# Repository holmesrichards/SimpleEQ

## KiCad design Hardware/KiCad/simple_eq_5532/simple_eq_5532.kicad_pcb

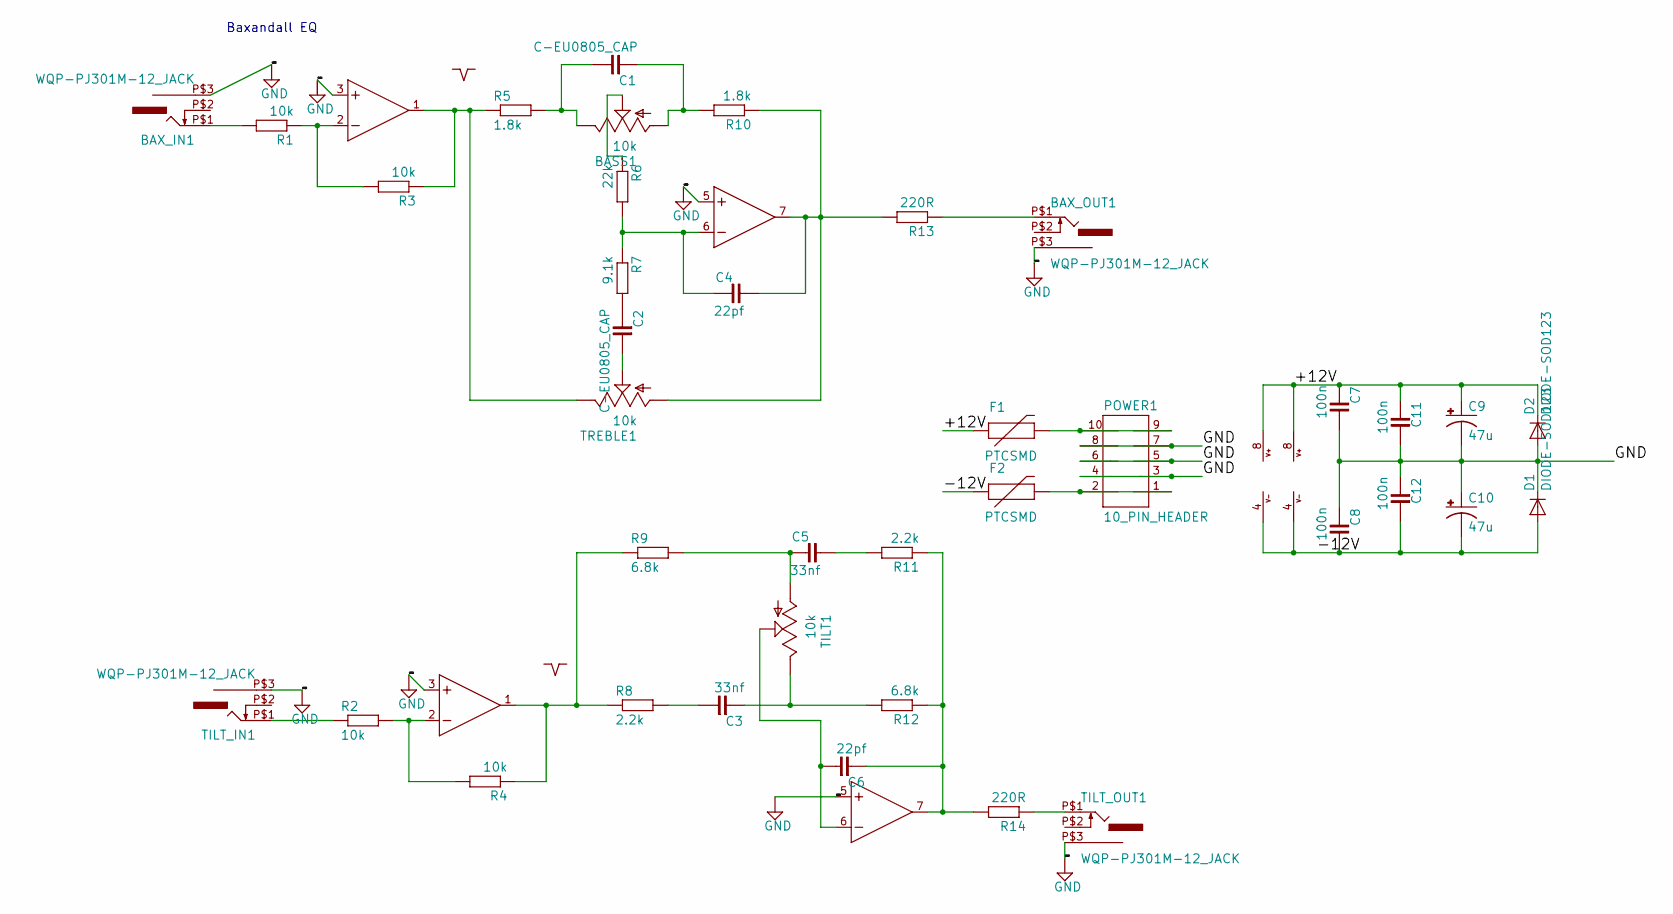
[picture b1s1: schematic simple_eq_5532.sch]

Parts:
BASS1: 10k; EVUF
BAX_IN1: WQP-PJ301M-12_JACK
BAX_OUT1: WQP-PJ301M-12_JACK
C1, C2: C-EU0805_CAP; R0805
C3, C5: 33nf; R0805
C4, C6: 22pf; R0805
C7, C8, C11, C12: 100n; R0805
C9, C10: 47u; PANASONIC_D
D1, D2: DIODE-SOD123; SOD123
F1, F2: PTCSMD; PTC-1206
IC1, IC2: NE5532; SO08
POWER1: 10_PIN_HEADER; MA05-2
R1, R2, R3, R4: 10k; R0805
R5, R10: 1.8k; R0805
R6: 22k; R0805
R7: 9.1k; R0805
R8, R11: 2.2k; R0805
R9, R12: 6.8k; R0805
R13, R14: 220R; R0805
TILT1: 10k; EVUF
TILT_IN1: WQP-PJ301M-12_JACK
TILT_OUT1: WQP-PJ301M-12_JACK
TREBLE1: 10k; EVUF

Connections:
/+12V: C7.2, C9.+, C11.2, D2.C, F1.1, IC1.8 (V+), IC2.8 (V+)
/-12V: C8.1, C10.-, C12.1, D1.A, F2.1, IC1.4 (V-), IC2.4 (V-)
GND: BAX_IN1.P$3 (1), BAX_OUT1.P$3 (1), C7.1, C8.2, C9.-, C10.+, C11.1, C12.2, D1.C, D2.A, IC1.3 (+IN), IC1.5 (+IN), IC2.3 (+IN), IC2.5 (+IN), POWER1.3, POWER1.4, POWER1.5, POWER1.6, POWER1.7, POWER1.8, TILT_IN1.P$3 (1), TILT_OUT1.P$3 (1)
unnamed: BASS1.1 (A), C1.2, R10.2
unnamed: BASS1.2 (S), R6.1
unnamed: BASS1.3 (E), C1.1, R5.2
unnamed: BAX_IN1.P$1 (2), R1.2
unnamed: BAX_OUT1.P$1 (2), R13.1
unnamed: C2.1, TREBLE1.2 (S)
unnamed: C2.2, R7.2
unnamed: C3.1, R8.2
unnamed: C3.2, R12.2, TILT1.3 (E)
unnamed: C4.1, IC1.7 (OUT), R10.1, R13.2, TREBLE1.1 (A)
unnamed: C4.2, IC1.6 (-IN), R6.2, R7.1
unnamed: C5.1, R11.2
unnamed: C5.2, R9.2, TILT1.1 (A)
unnamed: C6.1, IC2.6 (-IN), TILT1.2 (S)
unnamed: C6.2, IC2.7 (OUT), R11.1, R12.1, R14.2
unnamed: F1.2, POWER1.9, POWER1.10
unnamed: F2.2, POWER1.1, POWER1.2
unnamed: IC1.1 (OUT), R3.1, R5.1, TREBLE1.3 (E)
unnamed: IC1.2 (-IN), R1.1, R3.2
unnamed: IC2.1 (OUT), R4.1, R8.1, R9.1
unnamed: IC2.2 (-IN), R2.2, R4.2
unnamed: R2.1, TILT_IN1.P$1 (2)
unnamed: R14.1, TILT_OUT1.P$1 (2)

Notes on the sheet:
Baxandall EQ

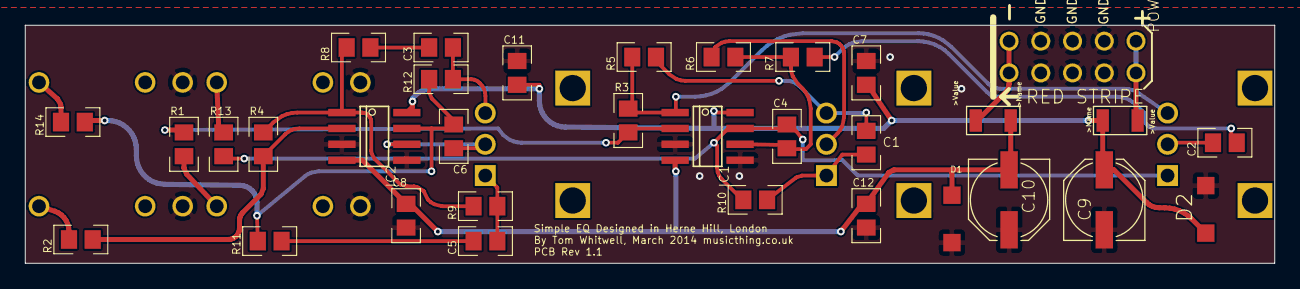
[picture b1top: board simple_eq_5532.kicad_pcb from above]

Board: 4 copper layers, 100.0 x 19.0 mm, 43 parts (0 on the bottom side), 26 nets.

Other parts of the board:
U$5: MTM_1CM
U$6: CC_1CM_SCREENPRINT
U$7: THONK_1CM_SCREENPRINT

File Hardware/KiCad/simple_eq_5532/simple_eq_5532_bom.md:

# simple_eq_5532 BOM

Wed 07 Oct 2020 05:36:12 PM EDT

Generated from schematic by Eeschema 5.1.6-c6e7f7d~87~ubuntu20.04.1

**Component Count:** 40

| Value | Qty | Part | Description | Vendor |
| ----- | --- | ---- | ----------- | ------ |
| BASS1, TILT1, TREBLE1 | 3 | 10k | 9mm vertical |  |
| BAX_IN1, BAX_OUT1, TILT_IN1, TILT_OUT1 | 4 | WQP-PJ301M-12_JACK | 3.5mm jack |  |
| C1, C7, C8, C11, C12 | 4 | 100nF | 0805 |  |
| C2 | 2 | 4.7nF | 0805 |  |
| C3, C5 | 2 | 33nF | 0805 |  |
| C4, C6 | 2 | 22pF | 0805 |  |
| C9, C10 | 2 | 47uF | Panasonic_D |  |
| D1, D2 | 2 | 1n5819 | SOD123 |  |
| F1, F2 | 2 | PTCSMD |  |  |
| IC1, IC2 | 2 | NE5532 | SO08 |  |
| POWER1 | 1 | 10_PIN_HEADER | Through hole  |  |
| R1, R2, R3, R4 | 4 | 10k | 0805 |  |
| R5, R10 | 3 | 1.8k | 0805 |  |
| R7 | 3 | 9.1k | 0805 |  |
| R6 | 1 | 22k | 0805 |  |
| R8, R11 | 2 | 2.2k | 0805 |  |
| R9, R12 | 2 | 6.8k | 0805 |  |
| R13, R14 | 2 | 220R | 0805 |  |

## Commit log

2020-10-07 KiCad, BOM, value corrections
